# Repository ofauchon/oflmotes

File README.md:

# oflmotes

New 802.15.4 Sensor Network Framework.
OFLmotes is is the sucessor of OFLmetrics project. 

It's a full rewrite of both embedded firmwares and server code. 
It's now based on RIOT-OS, Golang.

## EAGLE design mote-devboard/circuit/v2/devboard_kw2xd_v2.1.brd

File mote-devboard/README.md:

# v1.0 Hardware 

First design, proof of concept.

# v2.0 Hardware

<!---->

Enhancements: 

- 1 Led connected to power
- 2 Leds connected to GPIO
- 2 Buttons connected to GPIO
- Reduced board size
- AAA Batteries Support

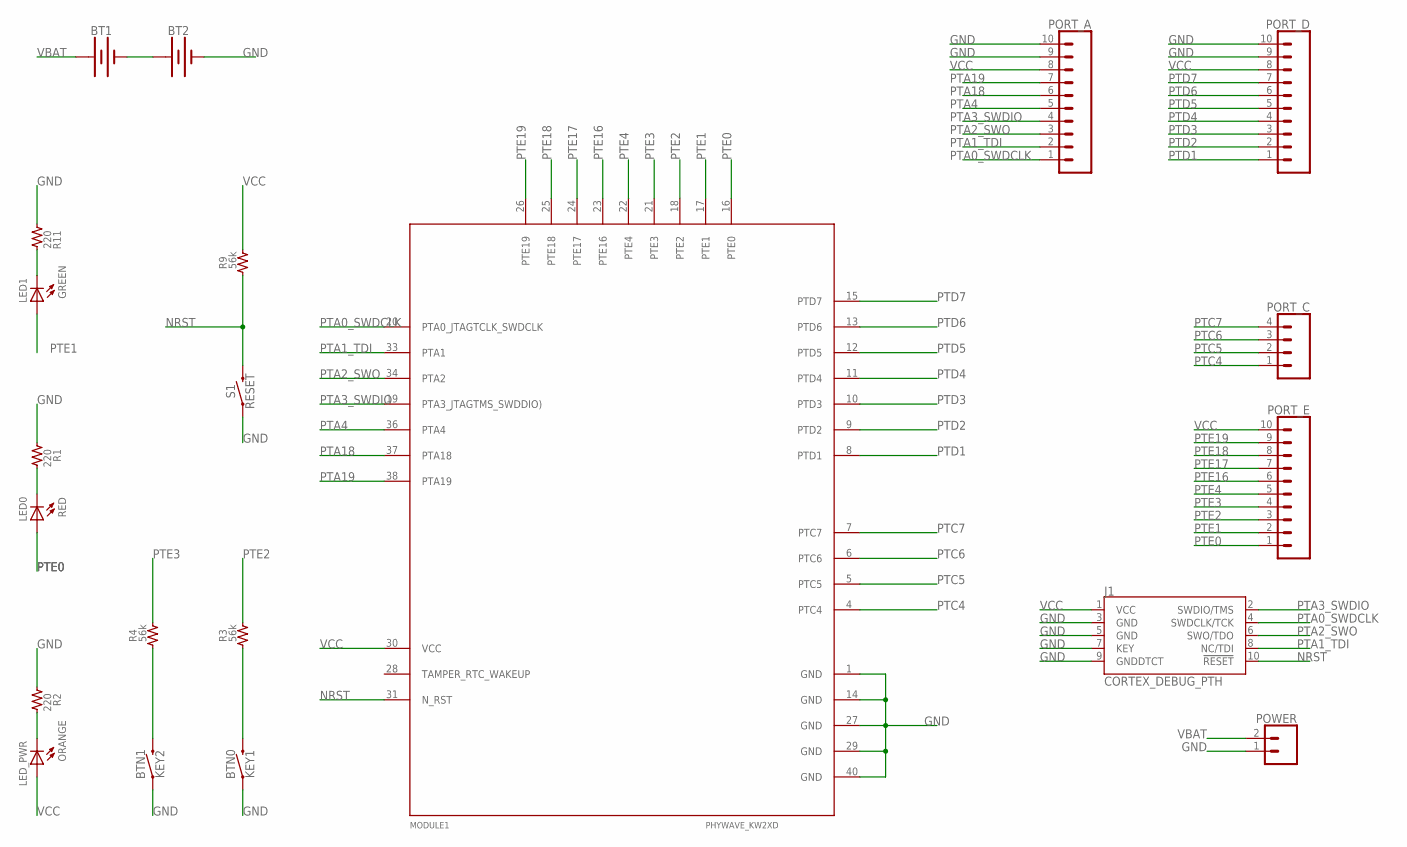
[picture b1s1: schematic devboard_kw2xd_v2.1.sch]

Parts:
BT1, BT2: BATTERY-AAA
BTN0: KEY1; TACTILE_SWITCH_SMD_4.6X2.8MM
BTN1: KEY2; TACTILE_SWITCH_SMD_4.6X2.8MM
J1: CORTEX_DEBUG_PTH; 2X5-PTH-1.27MM
LED0: RED; LED0603
LED1: GREEN; LED0603
LED_PWR: ORANGE; LED0603
MODULE1: PHYWAVE_KW2XD
PORT_A: CONN_10"; 1X10
PORT_C: CONN_04; 1X04
PORT_D: CONN_10"; 1X10
PORT_E: CONN_10"; 1X10
POWER: CONN_02; 1X02
R1, R2, R11: 220; SMD0603
R3, R4, R9: 56k; SMD0603
S1: RESET; TACTILE_SWITCH_SMD_4.6X2.8MM

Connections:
GND: BT2.GND@1 (-), BTN0.1, BTN0.2 (1), BTN1.1, BTN1.2 (1), J1.3 (GND), J1.5 (GND), J1.7 (KEY), J1.9 (GNDDTCT), MODULE1.1 (GND), MODULE1.14 (GND), MODULE1.27 (GND), MODULE1.29 (GND), MODULE1.40 (GND), PORT_A.9, PORT_A.10, PORT_D.9, PORT_D.10, POWER.1, R1.1, R2.1, R11.1, S1.1, S1.2 (1)
unnamed: LED0.C, R1.2
unnamed: LED_PWR.C, R2.2
unnamed: BT1.GND@1 (-), BT2.PWR@1 (+)
unnamed: LED1.C, R11.2
NRST: BTN0.3 (2), BTN0.4 (2), J1.10 (!RESET), MODULE1.31 (N_RST), R3.1, R9.1, S1.3 (2), S1.4 (2)
NRST1: BTN1.3 (2), BTN1.4 (2), R4.1
PTA0_SWDCLK: J1.4 (SWDCLK/TCK), MODULE1.20 (PTA0_JTAGTCLK_SWDCLK), PORT_A.1
PTA1_TDI: J1.8 (NC/TDI), MODULE1.33 (PTA1), PORT_A.2
PTA2_SWO: J1.6 (SWO/TDO), MODULE1.34 (PTA2), PORT_A.3
PTA3_SWDIO: J1.2 (SWDIO/TMS), MODULE1.19 (PTA3_JTAGTMS_SWDDIO)), PORT_A.4
PTA4: MODULE1.36 (PTA4), PORT_A.5
PTA18: MODULE1.37 (PTA18), PORT_A.6
PTA19: MODULE1.38 (PTA19), PORT_A.7
PTC4: MODULE1.4 (PTC4), PORT_C.1
PTC5: MODULE1.5 (PTC5), PORT_C.2
PTC6: MODULE1.6 (PTC6), PORT_C.3
PTC7: MODULE1.7 (PTC7), PORT_C.4
PTD1: MODULE1.8 (PTD1), PORT_D.1
PTD2: MODULE1.9 (PTD2), PORT_D.2
PTD3: MODULE1.10 (PTD3), PORT_D.3
PTD4: MODULE1.11 (PTD4), PORT_D.4
PTD5: MODULE1.12 (PTD5), PORT_D.5
PTD6: MODULE1.13 (PTD6), PORT_D.6
PTD7: MODULE1.15 (PTD7), PORT_D.7
PTE0: LED0.A, MODULE1.16 (PTE0), PORT_E.1
PTE1: LED1.A, MODULE1.17 (PTE1), PORT_E.2
PTE2: MODULE1.18 (PTE2), PORT_E.3, R3.2
PTE3: MODULE1.21 (PTE3), PORT_E.4, R4.2
PTE4: MODULE1.22 (PTE4), PORT_E.5
PTE16: MODULE1.23 (PTE16), PORT_E.6
PTE17: MODULE1.24 (PTE17), PORT_E.7
PTE18: MODULE1.25 (PTE18), PORT_E.8
PTE19: MODULE1.26 (PTE19), PORT_E.9
VBAT: BT1.PWR@1 (+), POWER.2
VCC: J1.1 (VCC), LED_PWR.A, MODULE1.30 (VCC), PORT_A.8, PORT_D.8, PORT_E.10, R9.2

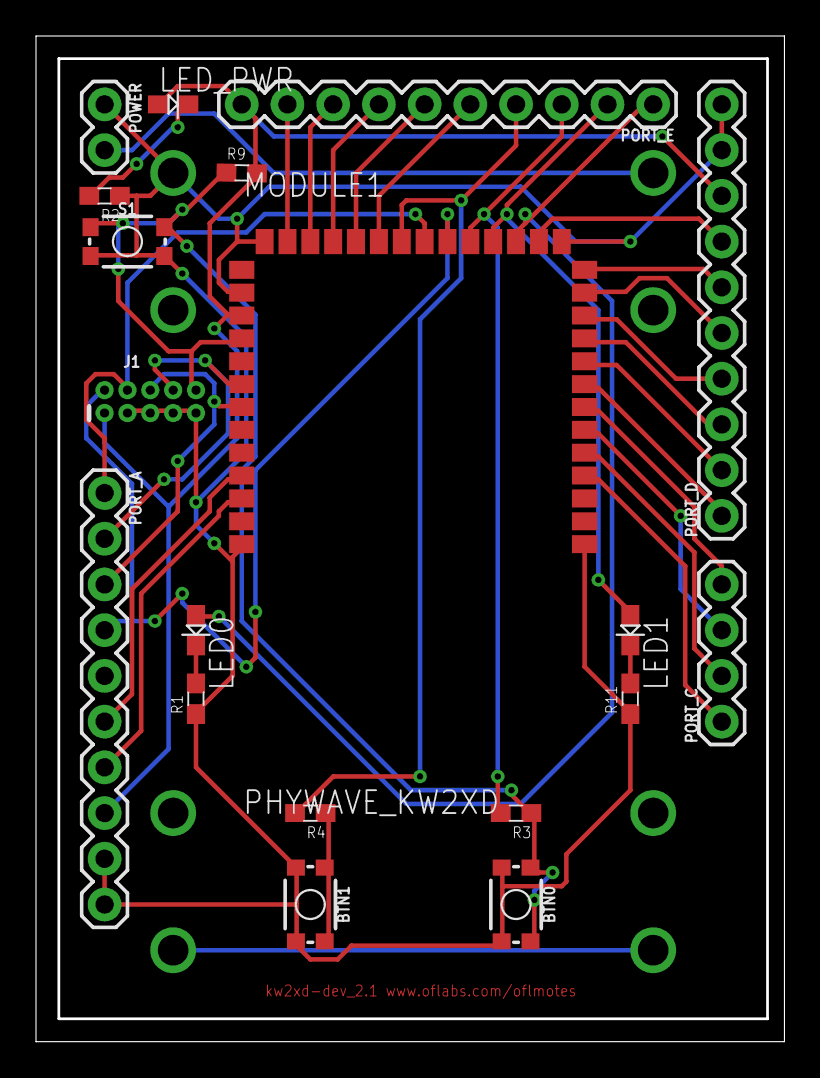
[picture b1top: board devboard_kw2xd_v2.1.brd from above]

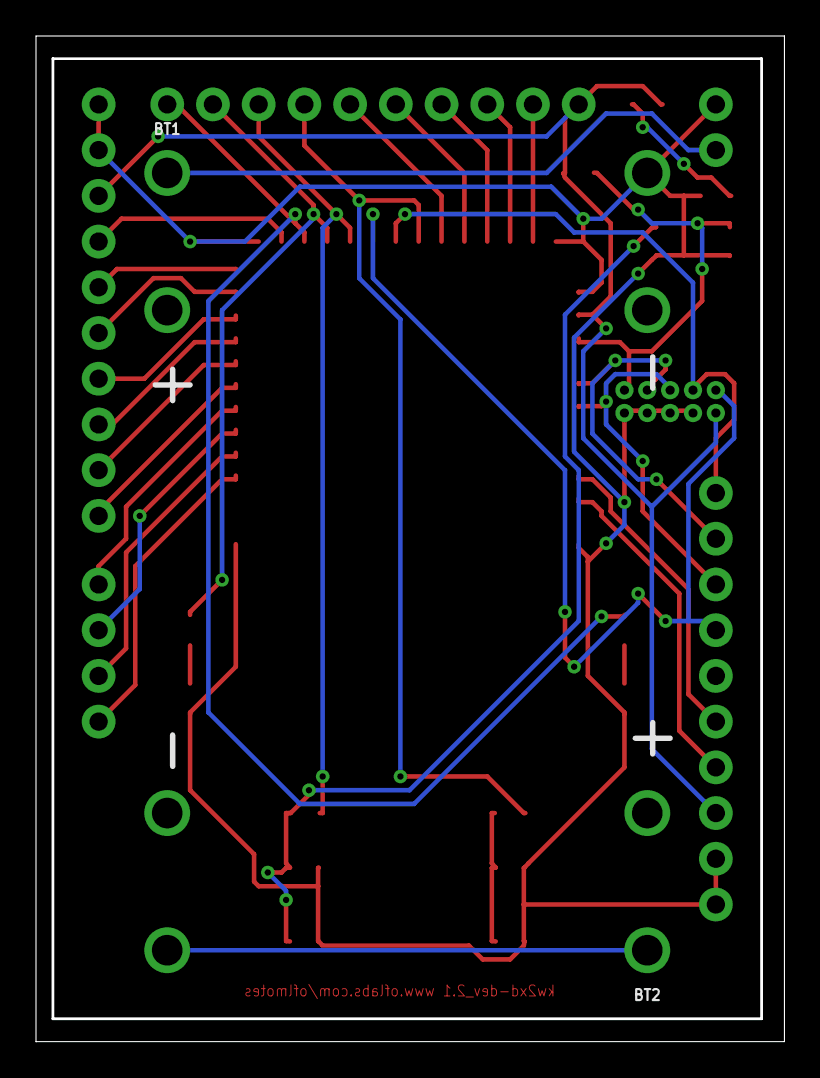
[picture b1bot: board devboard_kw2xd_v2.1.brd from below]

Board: 2 copper layers, 41.4 x 55.7 mm, 21 parts (2 on the bottom side), 36 nets.

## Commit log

2017-10-15 Initial version import
2017-10-15 Minor updates
2017-10-19 Code cleanup and fixes. Packet RX dump works now
2017-10-19 Move code from mote-gateway/ to mote-gateway/hard , so I can create a mote-gateway/soft for the Linux server application
2017-10-19 Minor changes (email in sources, gitignore addition)
2017-10-19 Added compact dump to make parsing easier
2017-10-19 Initial version of mote-gateway .. Code needs serious cleanup/rewrite
2017-10-21 Command line for influxdb configuration and frames parsing
2017-10-21 Fix for TEMP metric decoding in frame, and properly handling influxdb types
2017-10-21 Code cleanup
2017-10-22 Bug in processing buffer
2017-10-22 Added start.sh script
2017-10-25 More logs cleanup
2017-10-25 Added snip loop
2017-10-27 Switch to 802.15.4 extended addressing (64bits) both hard and soft code
2017-10-27 Enhanced logs
2017-10-28 Changed 802.4.15 addressing to 16bit Pan + 64bit Addr
2017-10-29 Revert smac/dmac byte order
2017-10-29 Major improvements (handling pan/address/pktdump command. Promisc/Raw mode not required anymore
2017-10-30 Enhanced communication, added lqi and rssi
2017-10-30 Added lqi,rssi in metrics
2018-02-13 go fmt
2018-02-13 Fix minor log format error
2018-02-20 added -log command line flag
2018-03-04 Code fixups due to RIOT API Changes
2018-03-04 about command to display build informations
2018-03-04 Added README.md
2018-03-05 Bugfix when interface iteration
2018-03-09 First attempt to use Riot and pba-d-01-kw2x as teleinfo sensor
2018-03-10 Added Teleinfo protocol details
2018-03-15 Code cleanup, and fixes. Almost works but still WIP
2018-03-15 Display git build version at startup
2018-03-24 Added support for two PitInfo
2018-03-27 Reorganize source code for sensors
2018-03-27 README.md update
2018-03-27 More documentation
2018-04-17 Added logs and minor changes
2018-04-17 Initial changes to use rtt_timer in replacement of xtimer for better powersave
2018-04-27 - Added battery voltage measurement
2018-05-03 More code cleanup
2018-05-05 Add periodic transmission of technical informations like type of device, version, battery level
2018-05-05 More details about the project
2018-06-13 First Eagle PCB developpement board based on phyWAVE-KW2xD module
2018-06-14 - Add .brd board layout file
2018-06-14 -Increased clearances from 6 to 8mil to fit Eurocircuits PCB Manufacturer's requirements - Order a first batch of 2 naked prototype boards
2018-08-06 Added schematic and board pdf
2018-08-16 Some details in readme.md
2018-08-16 Picture of v1.0 board
2018-08-16 Added picture of v1.0 board
2018-08-16 Resize picture
2018-08-16 Added KW2xD module pinout
2018-08-16 Update TODO
2018-10-31 Added RIOT local board definition and a couple of examples
2018-10-31 Removed unused files
2018-11-08 Moved Eagle files to circuit/
2018-11-11 Versionning the current circuit design to v1
2018-11-14 Board v2
2018-11-30 test
    test
2018-12-08 Cleanup
2018-12-09 - Fix RSSI values in pktdump - Code indent
2018-12-09 Fix RSSI handling
2018-12-14 - Ignore .job eagle files
2018-12-14 2-pin header (upper left) will be used as power switch/current meter
2018-12-14 - Enhanced Readme
2018-12-14 - Board References moved to top copper layer
2018-12-14 Fix path to images
2018-12-14 Updare README
2018-12-14 README Updates
2018-12-14 Added v2 circuit
2018-12-14 Added board pcb
2018-12-14 Higher resolution for board pcb
2018-12-14 Added v2.1 circuit and pcb images
2018-12-17 Fix typo : Both buttons can be used to activate safeguard
2018-12-19 Use i2c0 PE18/PE19 instead of i2c1 PE0/PE1
2018-12-19 Change LED/PIN to PTE0/1/2/3
2018-12-20 LED OFF at boot
2018-12-20 lowpower test code
2019-01-01 Changed cpu mode to FEI so we don't rely on radio clock Minor changes in board design
2019-01-01 Revert i2c pin change
2019-01-01 Revert i2c pin change (forgot the MUX in previous commit)
2019-01-01 Change LEDs pin from PE0/PE1 to PD5/PD4 to free i2c ports (PE0/PE1)
2019-01-02 Added picocom target in Makefile
2019-01-02 Code cleanup, Added pm_block/pm_unblock
2019-01-02 Makefile USEMODULE Cleanup
2019-01-02 Remove unused, conflicting code PE2/PE3 are not anymore used to power up i2c device
2019-01-02 renamed radio-test to node-bme280
2019-01-02 Minor Makefile changes to fit new directory name and code cleanup
2019-01-03 Minore changes, cleanup logs
2019-01-06 Removed blinker thread, and don't turn off radio
2019-01-08 Added DEFINEs for Radio Sleep and power management
2019-01-08 Renamed powersave defines
2019-01-09 Build information display fixes
2019-01-09 TEST 1: No Hibernate, No radio Off
2019-01-09 Fix powersave bug
2019-01-09 Rewrite of mcu sleep and radio_off sections
2019-01-15 Use NETOPT_STATE_RESET before NETOPT_STATE_IDLE after radio wake up from hibernate
2019-01-18 - go fmt - Replaced log.Fatal with doLog
2019-01-20 More details in influx logs
2019-01-20 Added Influx HTTP Client Close Defer
2019-01-21 Fix log file bugs Added FIFO Buffer to handle InfluxDB transmissions failures
2019-01-22 Added picocom.log log file when running make picocom
2019-01-22 Added .gitignore
2019-01-22 Set max radio tx power
2019-01-29 Added Serial Read traces
2019-01-29 Improve README
2019-01-30 Minor changes (comments, leds usage)
2019-02-27 Added more debug
2019-03-04 Initial import
2019-03-20 Removed hello world example
2019-03-20 Debug messages, and re-enabling radio off at end of cycle
2019-03-22 Traces DEBUGs
2019-03-24 Use a state flag instead of PAPP,IINST,BASE values to detect end of processing
2019-03-27 Support for two teleinfo interfaces
2019-03-31 Dual teleinfo support fixes
2019-04-01 Replace multiple UART probing with one single multiplexed UART
2019-04-02 - Fixed state checks - Enhanced logs
2019-04-02 More doc
2019-06-18 Project Tree cleanup
2019-07-13 Add OpenOCD ftdi config fime
2019-07-14 Moved ftdi openocd config, create app/tests
2019-07-20 Update boads Makefile.features according to RIOT's pba-d-01-kw2x board
2019-07-20 Remove lots of pm_(un)block, no more required with latest RIOT code from Benemorius
2019-07-20 Openocd interface ftdi instead of jlink
2019-07-20 added test applications
2019-08-04 Lorawan - sx1276 tests
2019-08-16 Update UART llwu_rx PIN definition
2019-08-16 Removed unused Openocd initialization
2019-08-16 Update pacman requirements for build/debug
2019-08-16 node-sx1276 app code cleanup
2019-08-16 node-sx1276 Makefile cleanup
2019-08-16 Added custom openocf.cfg to oflomde-dev board definition
2019-08-16 Moved bood safeguard in an ifdef GUARD so it's optionnal

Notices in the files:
parts and their libraries:
SparkFun-Connectors: Licensing: Creative Commons ShareAlike 4.0 International - https://creativecommons.org/licenses/by-sa/4.0
